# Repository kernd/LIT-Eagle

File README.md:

Eagle-Libraries
===============

holds all eagle files - projects and libraries

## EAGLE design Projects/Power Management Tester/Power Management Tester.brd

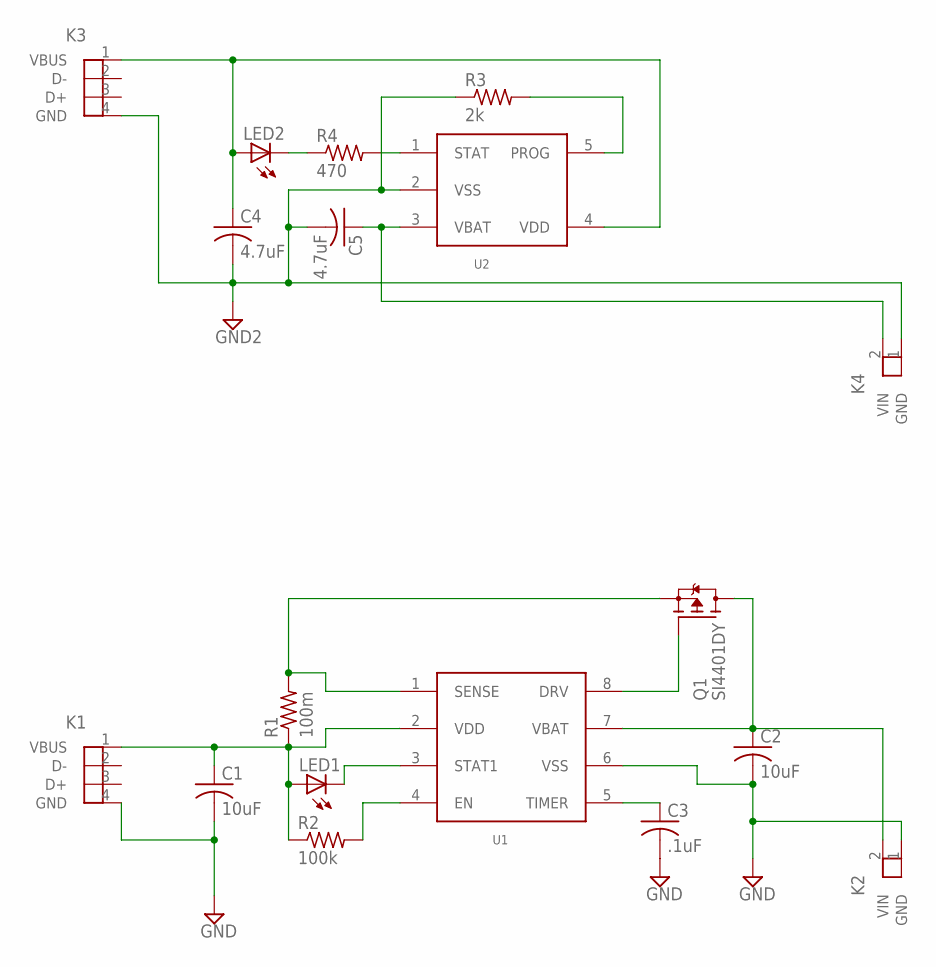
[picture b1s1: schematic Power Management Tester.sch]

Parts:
C1, C2: 10uF; 0805
C3: .1uF; 0603
C4, C5: 4.7uF; 0805
K1, K3: USBCONN; USB_RECEPT(CNC)
K2, K4: PWRCONN; 2CONN
LED1, LED2: LED0805; 0805
Q1: SI4401DY; 8-SOIC
R1: 100m; 0805
R2: 100k; 0603
R3: 2k; 0603
R4: 470; 0603
U1: MCP73843; 8-MSOP
U2: MCP73831; SOT-23

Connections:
5V_1: C1.A (1), K1.1 (VBUS), LED1.A (POS), R1.A (1), R2.1, U1.2 (VDD)
5V_2: C4.A (1), K3.1 (VBUS), LED2.A (POS), U2.4 (VDD)
D: C2.A (1), K2.2 (VIN), Q1.5 (D), Q1.6 (D), Q1.7 (D), Q1.8 (D), U1.7 (VBAT)
GND1: C1.A1 (2), C2.A1 (2), C3.2, K1.4 (GND), K2.1 (GND), U1.6 (VSS)
GND2: C4.A1 (2), C5.A1 (2), K3.4 (GND), K4.1 (GND), R3.1, U2.2 (VSS)
unnamed: C3.1, U1.5 (TIMER)
unnamed: LED2.A1 (NEG), R4.1
unnamed: R4.2, U2.1 (STAT)
unnamed: Q1.1 (S), Q1.2 (S), Q1.3 (S), R1.A1 (2), U1.1 (SENSE)
unnamed: LED1.A1 (NEG), U1.3 (STAT1)
unnamed: R2.2, U1.4 (EN)
unnamed: C5.A (1), K4.2 (VIN), U2.3 (VBAT)
unnamed: Q1.4 (G), U1.8 (DRV)
unnamed: R3.2, U2.5 (PROG)

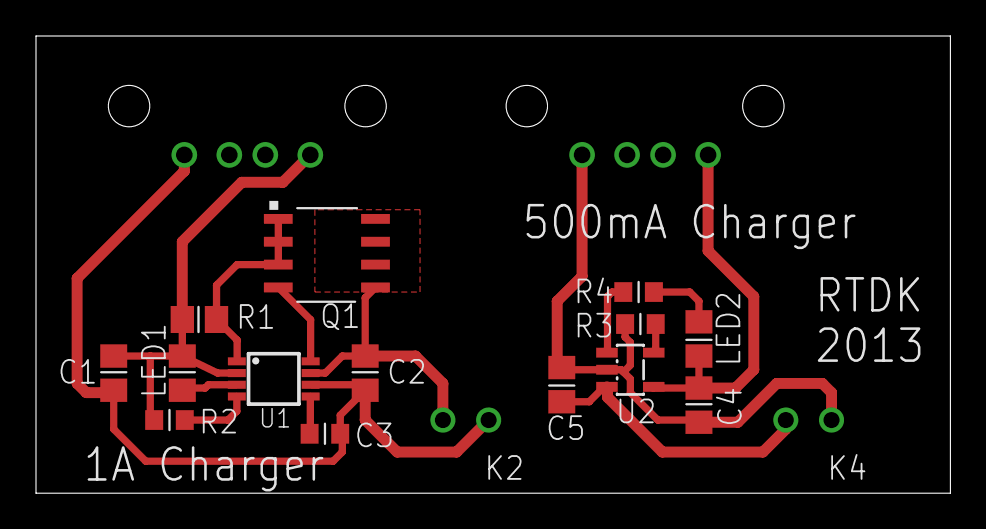
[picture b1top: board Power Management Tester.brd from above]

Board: 2 copper layers, 50.8 x 25.4 mm, 18 parts (0 on the bottom side), 14 nets.

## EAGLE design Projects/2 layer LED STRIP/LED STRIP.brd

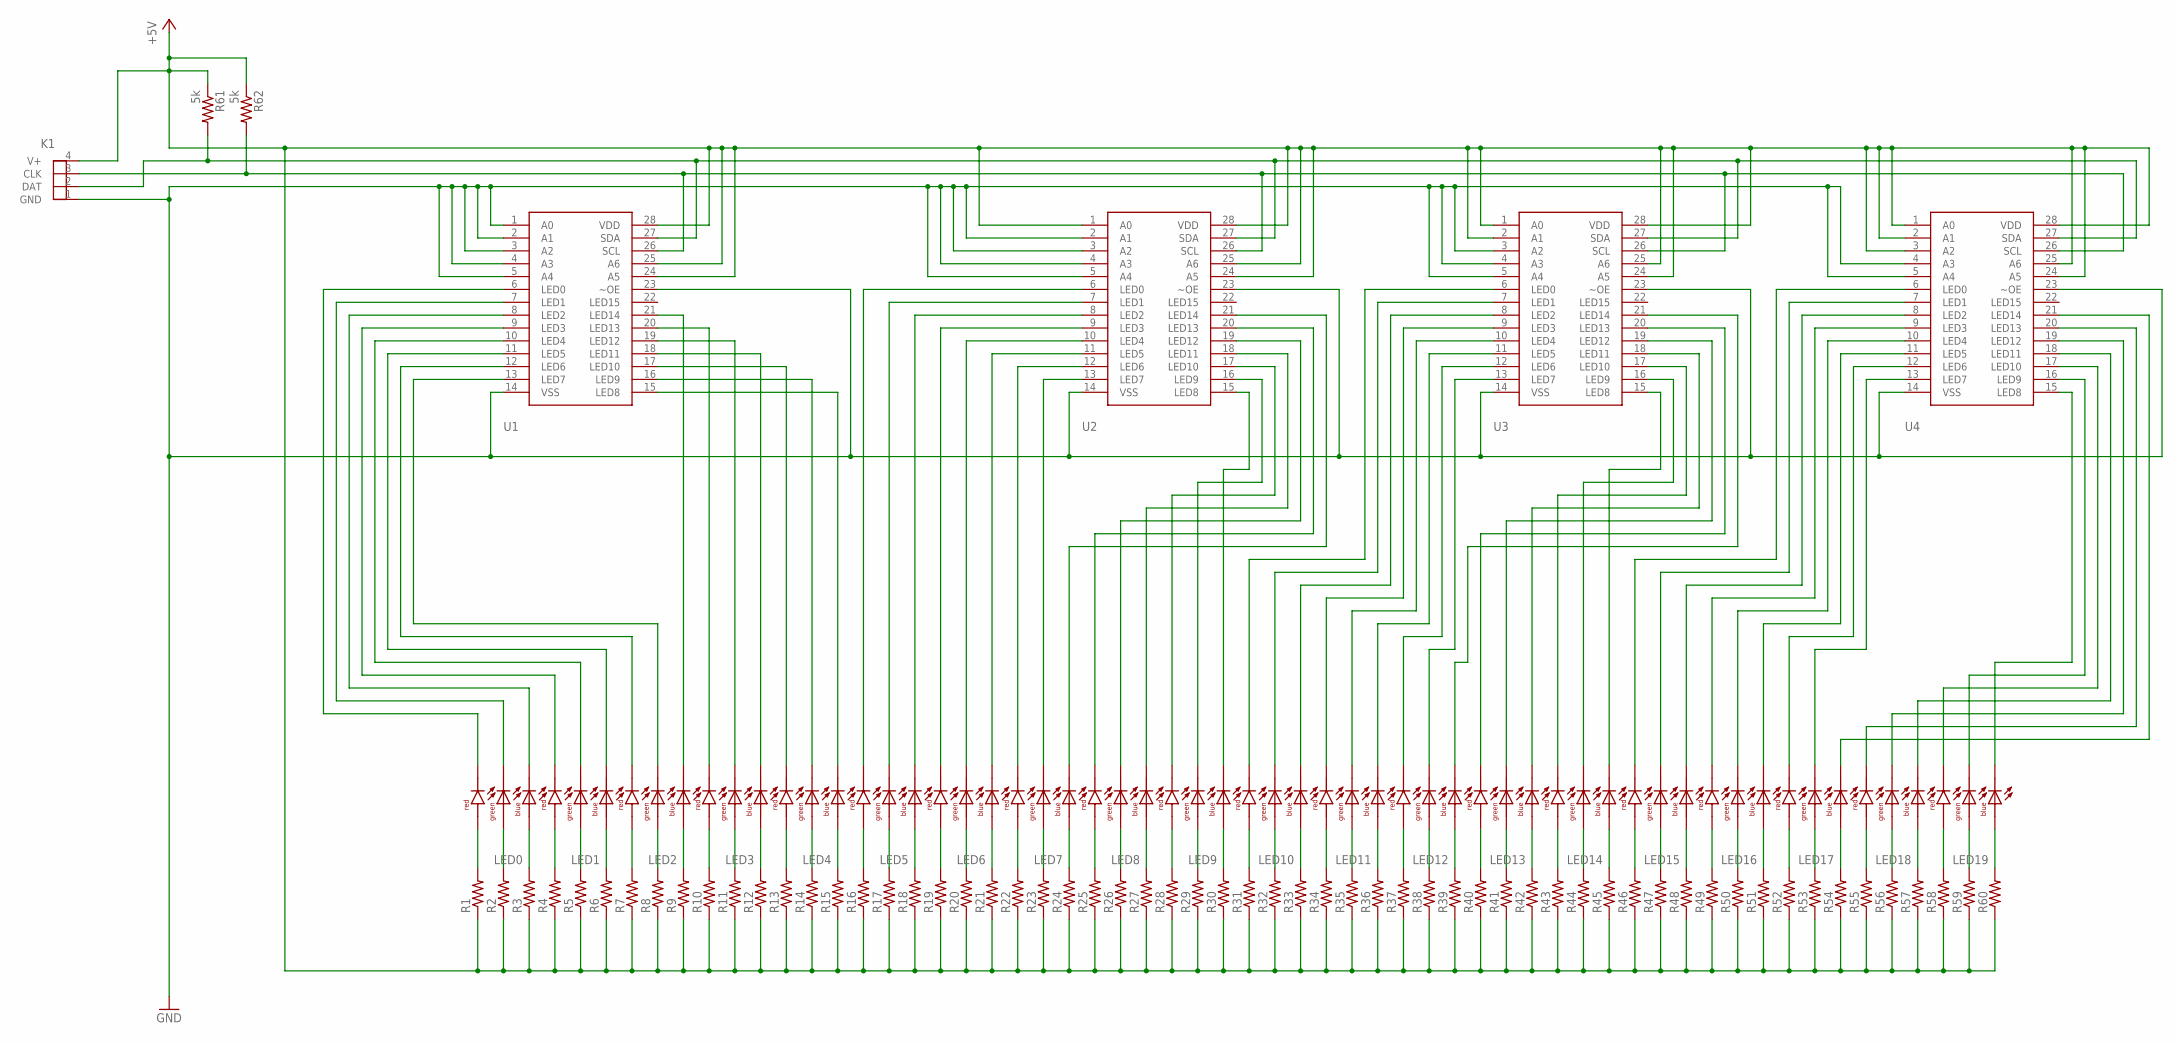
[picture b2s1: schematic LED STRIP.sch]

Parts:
K1: LEDCONN; 4CONN
LED0, LED1, LED2, LED3, LED4, LED5, LED6, LED7, LED8, LED9, LED10, LED11, LED12, LED13, LED14, LED15, LED16, LED17, LED18, LED19: LED_RGB; 6-PLCC
R1, R2, R3, R4, R5, R6, R7, R8, R9, R10, R11, R12, R13, R14, R15, R16, R17, R18, R19, R20, R21, R22, R23, R24, R25, R26, R27, R28, R29, R30, R31, R32, R33, R34, R35, R36, R37, R38, R39, R40, R41, R42, R43, R44, R45, R46, R47, R48, R49, R50, R51, R52, R53, R54, R55, R56, R57, R58, R59, R60: R0402; 0402
R61, R62: 5k; 0402
U1, U2, U3, U4: PCA9635; TSSOP28

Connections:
+5V: K1.4 (V+), R1.P$1 (1), R2.P$1 (1), R3.P$1 (1), R4.P$1 (1), R5.P$1 (1), R6.P$1 (1), R7.P$1 (1), R8.P$1 (1), R9.P$1 (1), R10.P$1 (1), R11.P$1 (1), R12.P$1 (1), R13.P$1 (1), R14.P$1 (1), R15.P$1 (1), R16.P$1 (1), R17.P$1 (1), R18.P$1 (1), R19.P$1 (1), R20.P$1 (1), R21.P$1 (1), R22.P$1 (1), R23.P$1 (1), R24.P$1 (1), R25.P$1 (1), R26.P$1 (1), R27.P$1 (1), R28.P$1 (1), R29.P$1 (1), R30.P$1 (1), R31.P$1 (1), R32.P$1 (1), R33.P$1 (1), R34.P$1 (1), R35.P$1 (1), R36.P$1 (1), R37.P$1 (1), R38.P$1 (1), R39.P$1 (1), R40.P$1 (1), R41.P$1 (1), R42.P$1 (1), R43.P$1 (1), R44.P$1 (1), R45.P$1 (1), R46.P$1 (1), R47.P$1 (1), R48.P$1 (1), R49.P$1 (1), R50.P$1 (1), R51.P$1 (1), R52.P$1 (1), R53.P$1 (1), R54.P$1 (1), R55.P$1 (1), R56.P$1 (1), R57.P$1 (1), R58.P$1 (1), R59.P$1 (1), R60.P$1 (1), R61.P$1 (1), R62.P$1 (1), U1.24 (A5), U1.25 (A6), U1.28 (VDD), U2.1 (A0), U2.24 (A5), U2.25 (A6), U2.28 (VDD), U3.1 (A0), U3.2 (A1), U3.24 (A5), U3.25 (A6), U3.28 (VDD), U4.1 (A0), U4.2 (A1), U4.3 (A2), U4.24 (A5), U4.25 (A6), U4.28 (VDD)
BLUE0: LED0.BLUE_LOW, U1.8 (LED2)
BLUE1: LED1.BLUE_LOW, U1.11 (LED5)
BLUE2: LED2.BLUE_LOW, U1.21 (LED14)
BLUE3: LED3.BLUE_LOW, U1.18 (LED11)
BLUE4: LED4.BLUE_LOW, U1.15 (LED8)
BLUE5: LED5.BLUE_LOW, U2.8 (LED2)
BLUE6: LED6.BLUE_LOW, U2.11 (LED5)
BLUE7: LED7.BLUE_LOW, U2.21 (LED14)
BLUE8: LED8.BLUE_LOW, U2.18 (LED11)
BLUE9: LED9.BLUE_LOW, U2.15 (LED8)
BLUE10: LED10.BLUE_LOW, U3.8 (LED2)
BLUE11: LED11.BLUE_LOW, U3.11 (LED5)
BLUE12: LED12.BLUE_LOW, U3.21 (LED14)
BLUE13: LED13.BLUE_LOW, U3.18 (LED11)
BLUE14: LED14.BLUE_LOW, U3.15 (LED8)
BLUE15: LED15.BLUE_LOW, U4.8 (LED2)
BLUE16: LED16.BLUE_LOW, U4.11 (LED5)
BLUE17: LED17.BLUE_LOW, U4.21 (LED14)
BLUE18: LED18.BLUE_LOW, U4.18 (LED11)
BLUE19: LED19.BLUE_LOW, U4.15 (LED8)
GND: K1.1 (GND), U1.1 (A0), U1.2 (A1), U1.3 (A2), U1.4 (A3), U1.5 (A4), U1.14 (VSS), U1.23 (~OE), U2.2 (A1), U2.3 (A2), U2.4 (A3), U2.5 (A4), U2.14 (VSS), U2.23 (~OE), U3.3 (A2), U3.4 (A3), U3.5 (A4), U3.14 (VSS), U3.23 (~OE), U4.4 (A3), U4.5 (A4), U4.14 (VSS), U4.23 (~OE)
GREEN0: LED0.GREEN_LOW, U1.7 (LED1)
GREEN1: LED1.GREEN_LOW, U1.10 (LED4)
GREEN2: LED2.GREEN_LOW, U1.13 (LED7)
GREEN3: LED3.GREEN_LOW, U1.19 (LED12)
GREEN4: LED4.GREEN_LOW, U1.16 (LED9)
GREEN5: LED5.GREEN_LOW, U2.7 (LED1)
GREEN6: LED6.GREEN_LOW, U2.10 (LED4)
GREEN7: LED7.GREEN_LOW, U2.13 (LED7)
GREEN8: LED8.GREEN_LOW, U2.19 (LED12)
GREEN9: LED9.GREEN_LOW, U2.16 (LED9)
GREEN10: LED10.GREEN_LOW, U3.7 (LED1)
GREEN11: LED11.GREEN_LOW, U3.10 (LED4)
GREEN12: LED12.GREEN_LOW, U3.13 (LED7)
GREEN13: LED13.GREEN_LOW, U3.19 (LED12)
GREEN14: LED14.GREEN_LOW, U3.16 (LED9)
GREEN15: LED15.GREEN_LOW, U4.7 (LED1)
GREEN16: LED16.GREEN_LOW, U4.10 (LED4)
GREEN17: LED17.GREEN_LOW, U4.13 (LED7)
GREEN18: LED18.GREEN_LOW, U4.19 (LED12)
GREEN19: LED19.GREEN_LOW, U4.16 (LED9)
unnamed: LED15.BLUE_HIGH, R48.P$2 (2)
unnamed: LED0.GREEN_HIGH, R2.P$2 (2)
unnamed: LED15.RED_HIGH, R46.P$2 (2)
unnamed: LED14.BLUE_HIGH, R45.P$2 (2)
unnamed: LED1.GREEN_HIGH, R5.P$2 (2)
unnamed: LED14.RED_HIGH, R43.P$2 (2)
unnamed: LED13.BLUE_HIGH, R42.P$2 (2)
unnamed: LED2.GREEN_HIGH, R8.P$2 (2)
unnamed: LED13.RED_HIGH, R40.P$2 (2)
unnamed: LED12.BLUE_HIGH, R39.P$2 (2)
unnamed: LED3.GREEN_HIGH, R11.P$2 (2)
unnamed: LED10.RED_HIGH, R31.P$2 (2)
unnamed: LED9.BLUE_HIGH, R30.P$2 (2)
unnamed: LED4.GREEN_HIGH, R14.P$2 (2)
unnamed: LED9.RED_HIGH, R28.P$2 (2)
unnamed: LED8.BLUE_HIGH, R27.P$2 (2)
unnamed: LED5.GREEN_HIGH, R17.P$2 (2)
unnamed: LED7.BLUE_HIGH, R24.P$2 (2)
unnamed: LED8.RED_HIGH, R25.P$2 (2)
unnamed: LED6.GREEN_HIGH, R20.P$2 (2)
unnamed: LED7.RED_HIGH, R22.P$2 (2)
unnamed: LED6.BLUE_HIGH, R21.P$2 (2)
unnamed: LED7.GREEN_HIGH, R23.P$2 (2)
unnamed: LED6.RED_HIGH, R19.P$2 (2)
unnamed: LED5.RED_HIGH, R16.P$2 (2)
unnamed: LED8.GREEN_HIGH, R26.P$2 (2)
unnamed: LED4.BLUE_HIGH, R15.P$2 (2)
unnamed: LED4.RED_HIGH, R13.P$2 (2)
unnamed: LED9.GREEN_HIGH, R29.P$2 (2)
unnamed: LED3.BLUE_HIGH, R12.P$2 (2)
unnamed: LED3.RED_HIGH, R10.P$2 (2)
unnamed: LED10.GREEN_HIGH, R32.P$2 (2)
unnamed: LED2.BLUE_HIGH, R9.P$2 (2)
unnamed: LED1.BLUE_HIGH, R6.P$2 (2)
unnamed: LED11.GREEN_HIGH, R35.P$2 (2)
unnamed: LED1.RED_HIGH, R4.P$2 (2)
unnamed: LED0.BLUE_HIGH, R3.P$2 (2)
unnamed: LED12.GREEN_HIGH, R38.P$2 (2)
unnamed: LED0.RED_HIGH, R1.P$2 (2)
unnamed: LED2.RED_HIGH, R7.P$2 (2)
unnamed: LED13.GREEN_HIGH, R41.P$2 (2)
unnamed: LED5.BLUE_HIGH, R18.P$2 (2)
unnamed: LED10.BLUE_HIGH, R33.P$2 (2)
unnamed: LED14.GREEN_HIGH, R44.P$2 (2)
unnamed: LED11.RED_HIGH, R34.P$2 (2)
unnamed: LED11.BLUE_HIGH, R36.P$2 (2)
unnamed: LED15.GREEN_HIGH, R47.P$2 (2)
unnamed: LED12.RED_HIGH, R37.P$2 (2)
unnamed: LED19.BLUE_HIGH, R60.P$2 (2)
unnamed: LED19.GREEN_HIGH, R59.P$2 (2)
unnamed: LED19.RED_HIGH, R58.P$2 (2)
unnamed: LED18.BLUE_HIGH, R57.P$2 (2)
unnamed: LED18.GREEN_HIGH, R56.P$2 (2)
unnamed: LED18.RED_HIGH, R55.P$2 (2)
unnamed: LED17.BLUE_HIGH, R54.P$2 (2)
unnamed: LED17.GREEN_HIGH, R53.P$2 (2)
unnamed: LED17.RED_HIGH, R52.P$2 (2)
unnamed: LED16.BLUE_HIGH, R51.P$2 (2)
unnamed: LED16.GREEN_HIGH, R50.P$2 (2)
unnamed: LED16.RED_HIGH, R49.P$2 (2)
RED0: LED0.RED_LOW, U1.6 (LED0)
RED1: LED1.RED_LOW, U1.9 (LED3)
RED2: LED2.RED_LOW, U1.12 (LED6)
RED3: LED3.RED_LOW, U1.20 (LED13)
RED4: LED4.RED_LOW, U1.17 (LED10)
RED5: LED5.RED_LOW, U2.6 (LED0)
RED6: LED6.RED_LOW, U2.9 (LED3)
RED7: LED7.RED_LOW, U2.12 (LED6)
RED8: LED8.RED_LOW, U2.20 (LED13)
RED9: LED9.RED_LOW, U2.17 (LED10)
RED10: LED10.RED_LOW, U3.6 (LED0)
RED11: LED11.RED_LOW, U3.9 (LED3)
RED12: LED12.RED_LOW, U3.12 (LED6)
RED13: LED13.RED_LOW, U3.20 (LED13)
RED14: LED14.RED_LOW, U3.17 (LED10)
RED15: LED15.RED_LOW, U4.6 (LED0)
RED16: LED16.RED_LOW, U4.9 (LED3)
RED17: LED17.RED_LOW, U4.12 (LED6)
RED18: LED18.RED_LOW, U4.20 (LED13)
RED19: LED19.RED_LOW, U4.17 (LED10)
SCL: K1.3 (CLK), R62.P$2 (2), U1.26 (SCL), U2.26 (SCL), U3.26 (SCL), U4.26 (SCL)
SDA: K1.2 (DAT), R61.P$2 (2), U1.27 (SDA), U2.27 (SDA), U3.27 (SDA), U4.27 (SDA)

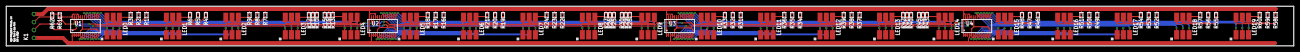
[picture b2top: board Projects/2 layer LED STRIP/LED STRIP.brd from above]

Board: 2 copper layers, 412.8 x 12.7 mm, 87 parts (0 on the bottom side), 124 nets.

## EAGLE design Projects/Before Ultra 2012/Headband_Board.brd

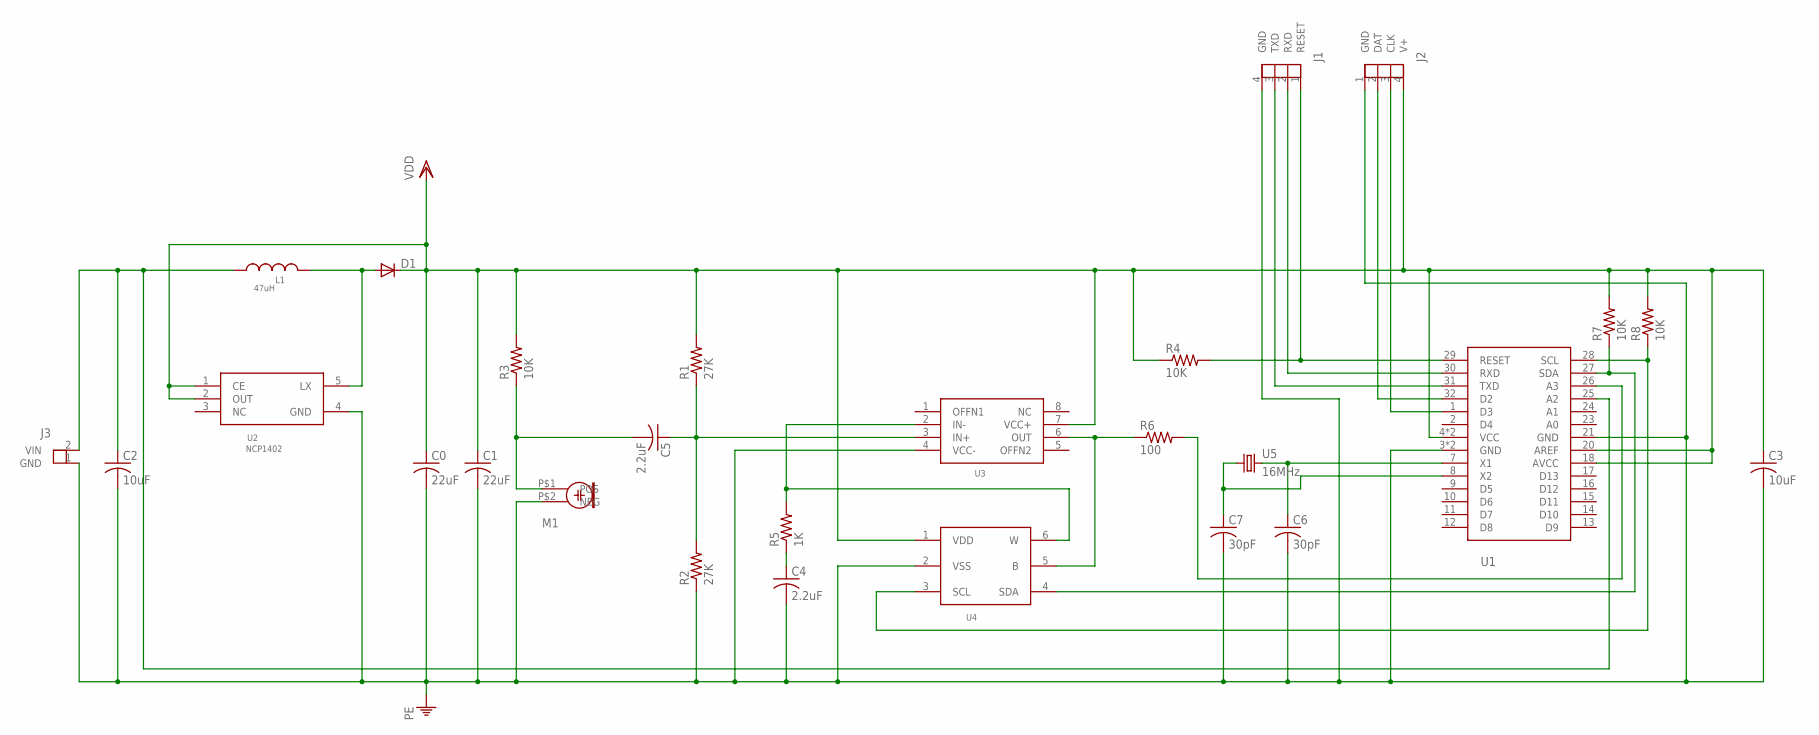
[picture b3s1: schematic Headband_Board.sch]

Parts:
C0, C1: 22uF; 0805
C2, C3: 10uF; 0805
C4, C5: 2.2uF; 0603
C6, C7: 30pF; 0603
D1: MBR0520LT; SOD-123
J1: PRGMCONN; 4CONN
J2: LEDCONN; 4CONN
J3: PWRCONN; 2CONN
L1: 47uH; INDUCPAC
M1: ELEC_MIC
R1, R2: 27K; 0603
R3, R4, R7, R8: 10K; 0603
R5: 1K; 0603
R6: 100; 0603
U1: ATMEGA328P; TQFP32-08
U2: NCP1402; TSOT-23-5
U3: TL071; 8-SOIC
U4: MCP4017; SOT-363
U5: 16MHz; HC49/US

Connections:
J1: J1.1 (RESET), R4.2, U1.29 (RESET)
unnamed: D1.A, L1.2, U2.5 (LX)
unnamed: C5.2, M1.P$1 (POS), R3.1
unnamed: R7.1, U1.27 (SDA), U4.4 (SDA)
unnamed: C5.1, R1.1, R2.2, U3.3 (IN+)
unnamed: R6.2, U1.26 (A3)
unnamed: C6.1, U1.7 (X1), U5.P$2 (2)
unnamed: C2.A (1), J3.2 (VIN), L1.3.7X1.2 (1), U1.25 (A2)
unnamed: J1.2 (RXD), U1.30 (RXD)
unnamed: C4.1, R5.1
unnamed: R5.2, U3.2 (IN-), U4.6 (W)
unnamed: J1.3 (TXD), U1.31 (TXD)
unnamed: R6.1, U3.6 (OUT), U4.5 (B)
unnamed: C7.1, U1.8 (X2), U5.P$1 (1)
unnamed: J2.2 (DAT), U1.32 (D2)
unnamed: J2.3 (CLK), U1.1 (D3)
unnamed: R8.1, U1.28 (SCL), U4.3 (SCL)
PE: C0.A1 (2), C1.A1 (2), C2.A1 (2), C3.A1 (2), C4.2, C6.2, C7.2, J1.4 (GND), J2.1 (GND), J3.1 (GND), M1.P$2 (NEG), R2.1, U1.3 (GND), U1.5 (GND), U1.21 (GND), U2.4 (GND), U3.4 (VCC-), U4.2 (VSS)
VDD: C0.A (1), C1.A (1), C3.A (1), D1.B, J2.4 (V+), R1.2, R3.2, R4.1, R7.2, R8.2, U1.4 (VCC), U1.6 (VCC), U1.18 (AVCC), U1.20 (AREF), U2.1 (CE), U2.2 (OUT), U3.7 (VCC+), U4.1 (VDD)

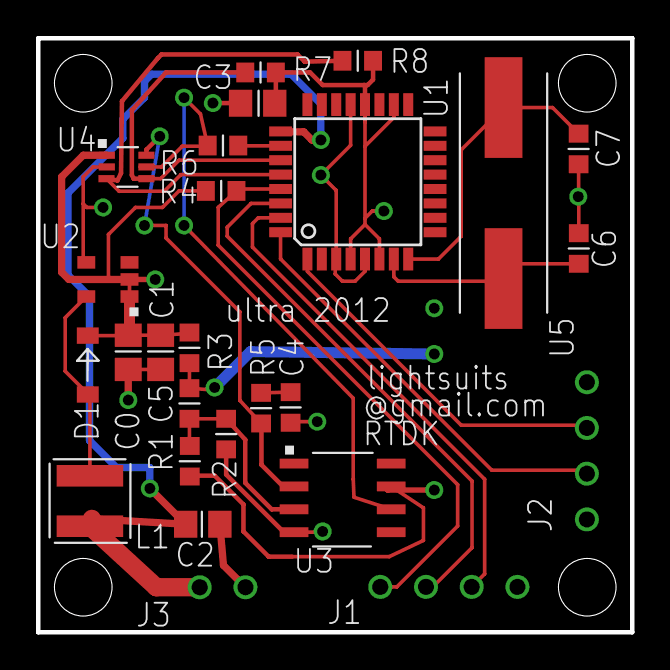
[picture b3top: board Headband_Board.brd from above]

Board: 2 copper layers, 33.0 x 33.0 mm, 27 parts (1 on the bottom side), 19 nets.

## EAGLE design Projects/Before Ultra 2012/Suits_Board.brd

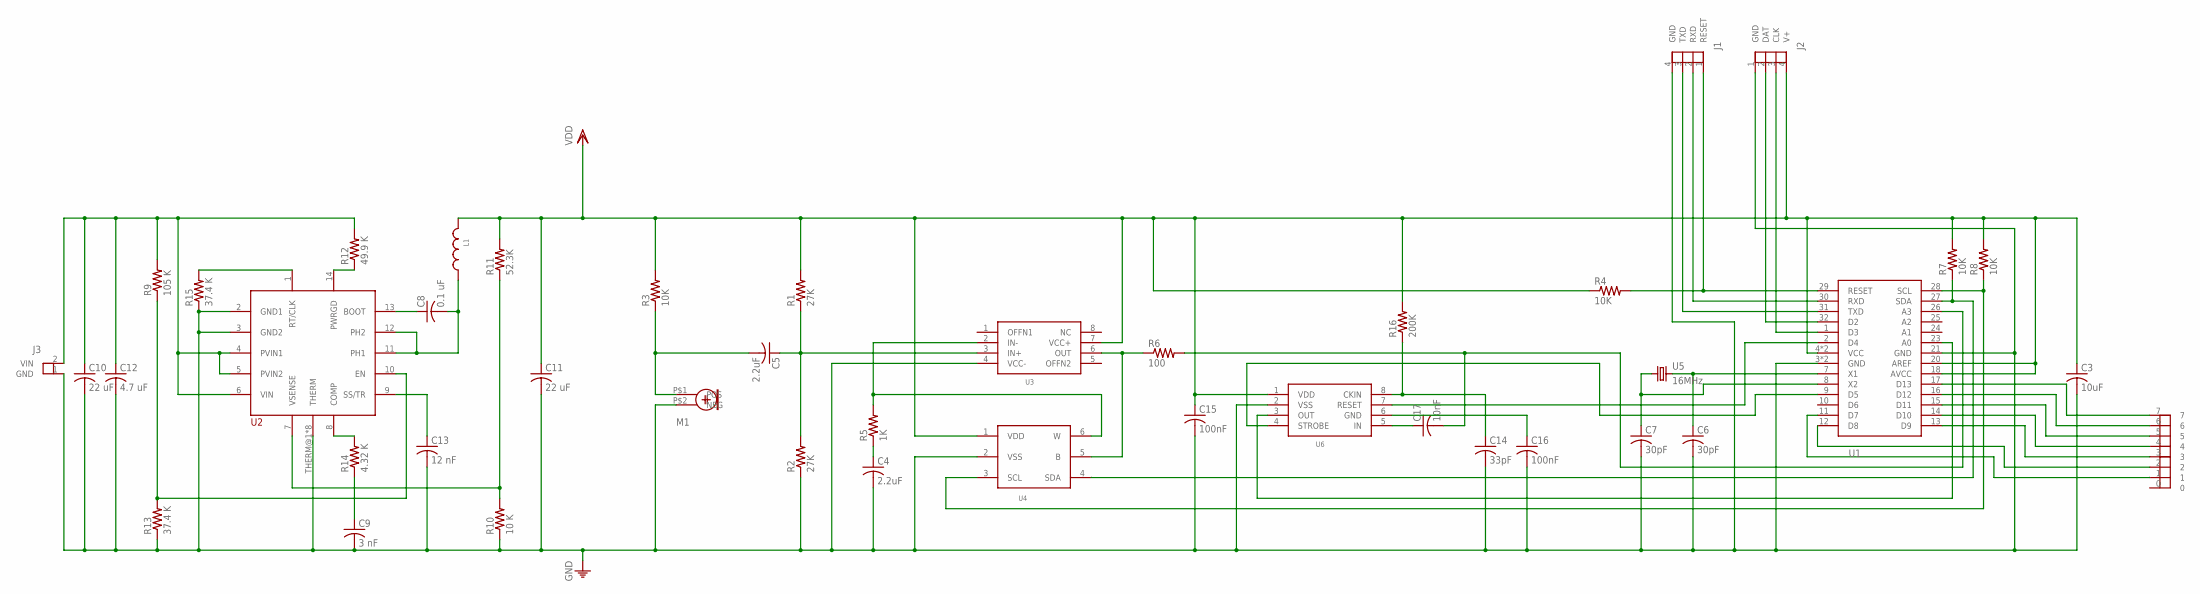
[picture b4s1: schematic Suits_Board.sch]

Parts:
C3: 10uF; 0805
C4, C5: 2.2uF; 0603
C6, C7: 30pF; 0603
C8: 0.1 uF; 0805
C9: 3 nF; 0805
C10, C11: 22 uF; 1210
C12: 4.7 uF; 0805
C13: 12 nF; 0402
C14: 33pF; 0402
C15, C16: 100nF; 0805
C17: 10nF; 0402
J1: PRGMCONN; 4CONN
J2: LEDCONN; 4CONN
J3: PWRCONN; 2CONN
L1: VLF10045T; VLF10045
M1: ELEC_MIC
R1, R2: 27K; 0603
R3, R4, R7, R8: 10K; 0603
R5: 1K; 0603
R6: 100; 0603
R9: 105 K; 0402
R10: 10 K; 0402
R11: 52.3K; 0402
R12: 49.9 K; 0402
R13, R15: 37.4 K; 0402
R14: 4.32 K; 0402
R16: 200K; 0603
U1: ATMEGA328P; TQFP32-08
U2: TPS54620; 14-VFQFN
U3: TL071; 8-SOIC
U4: MCP4017; SOT-363
U5: 16MHz; HC49/US
U6: FFT IC; DIP8
U$1: KEYPAD

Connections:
GND: C3.A1 (2), C4.2, C6.2, C7.2, C9.A1 (2), C10.P$2 (2), C11.P$2 (2), C12.A1 (2), C13.P$2 (2), C14.P$2 (2), C15.A1 (2), C16.A1 (2), J1.4 (GND), J2.1 (GND), J3.1 (GND), M1.P$2 (NEG), R2.1, R10.P$1 (1), R13.P$1 (1), R15.P$1 (1), U1.3 (GND), U1.5 (GND), U1.21 (GND), U2.2 (GND1), U2.3 (GND2), U2.THERM@1 (THERM), U2.THERM@2 (THERM), U2.THERM@3 (THERM), U2.THERM@4 (THERM), U2.THERM@5 (THERM), U2.THERM@6 (THERM), U2.THERM@7 (THERM), U2.THERM@8 (THERM), U3.4 (VCC-), U4.2 (VSS), U6.2 (VSS)
J1: J1.1 (RESET), R4.2, U1.29 (RESET)
unnamed: C14.P$1 (1), R16.1, U6.8 (CKIN)
unnamed: C16.A (1), U6.6 (GND)
unnamed: C5.2, M1.P$1 (POS), R3.1
unnamed: R7.1, U1.27 (SDA), U4.4 (SDA)
unnamed: C5.1, R1.1, R2.2, U3.3 (IN+)
unnamed: C17.P$2 (2), R6.2, U1.26 (A3)
unnamed: C6.1, U1.7 (X1), U5.P$2 (2)
unnamed: R14.P$2 (2), U2.8 (COMP)
unnamed: J1.2 (RXD), U1.30 (RXD)
unnamed: C4.1, R5.1
unnamed: R5.2, U3.2 (IN-), U4.6 (W)
unnamed: J1.3 (TXD), U1.31 (TXD)
unnamed: R6.1, U3.6 (OUT), U4.5 (B)
unnamed: U1.9 (D5), U6.4 (STROBE)
unnamed: J2.2 (DAT), U1.32 (D2)
unnamed: R9.P$1 (1), R13.P$2 (2), U2.10 (EN)
unnamed: J2.3 (CLK), U1.1 (D3)
unnamed: C9.A (1), R14.P$1 (1)
unnamed: R8.1, U1.28 (SCL), U4.3 (SCL)
unnamed: C13.P$1 (1), U2.9 (SS/TR)
unnamed: R15.P$2 (2), U2.1 (RT/CLK)
unnamed: R12.P$1 (1), U2.14 (PWRGD)
unnamed: C8.A1 (2), L1.P$1 (1), U2.11 (PH1), U2.12 (PH2)
unnamed: R10.P$2 (2), R11.P$1 (1), U2.7 (VSENSE)
unnamed: C8.A (1), U2.13 (BOOT)
unnamed: C17.P$1 (1), U6.5 (IN)
unnamed: U1.23 (A0), U6.3 (OUT)
unnamed: U1.17 (D13), U$1.7
unnamed: U1.15 (D11), U$1.5
unnamed: U1.16 (D12), U$1.6
unnamed: U1.14 (D10), U$1.4
unnamed: U1.13 (D9), U$1.3
unnamed: U1.12 (D8), U$1.2
unnamed: U1.11 (D7), U$1.1
unnamed: U1.2 (D4), U6.7 (RESET)
NAME\RIP: C7.1, U1.8 (X2), U5.P$1 (1)
VDD: C3.A (1), C11.P$1 (1), C15.A (1), J2.4 (V+), L1.P$2 (2), R1.2, R3.2, R4.1, R7.2, R8.2, R11.P$2 (2), R16.2, U1.4 (VCC), U1.6 (VCC), U1.18 (AVCC), U1.20 (AREF), U3.7 (VCC+), U4.1 (VDD), U6.1 (VDD)
VIN: C10.P$1 (1), C12.A (1), J3.2 (VIN), R9.P$2 (2), R12.P$2 (2), U2.4 (PVIN1), U2.5 (PVIN2), U2.6 (VIN)

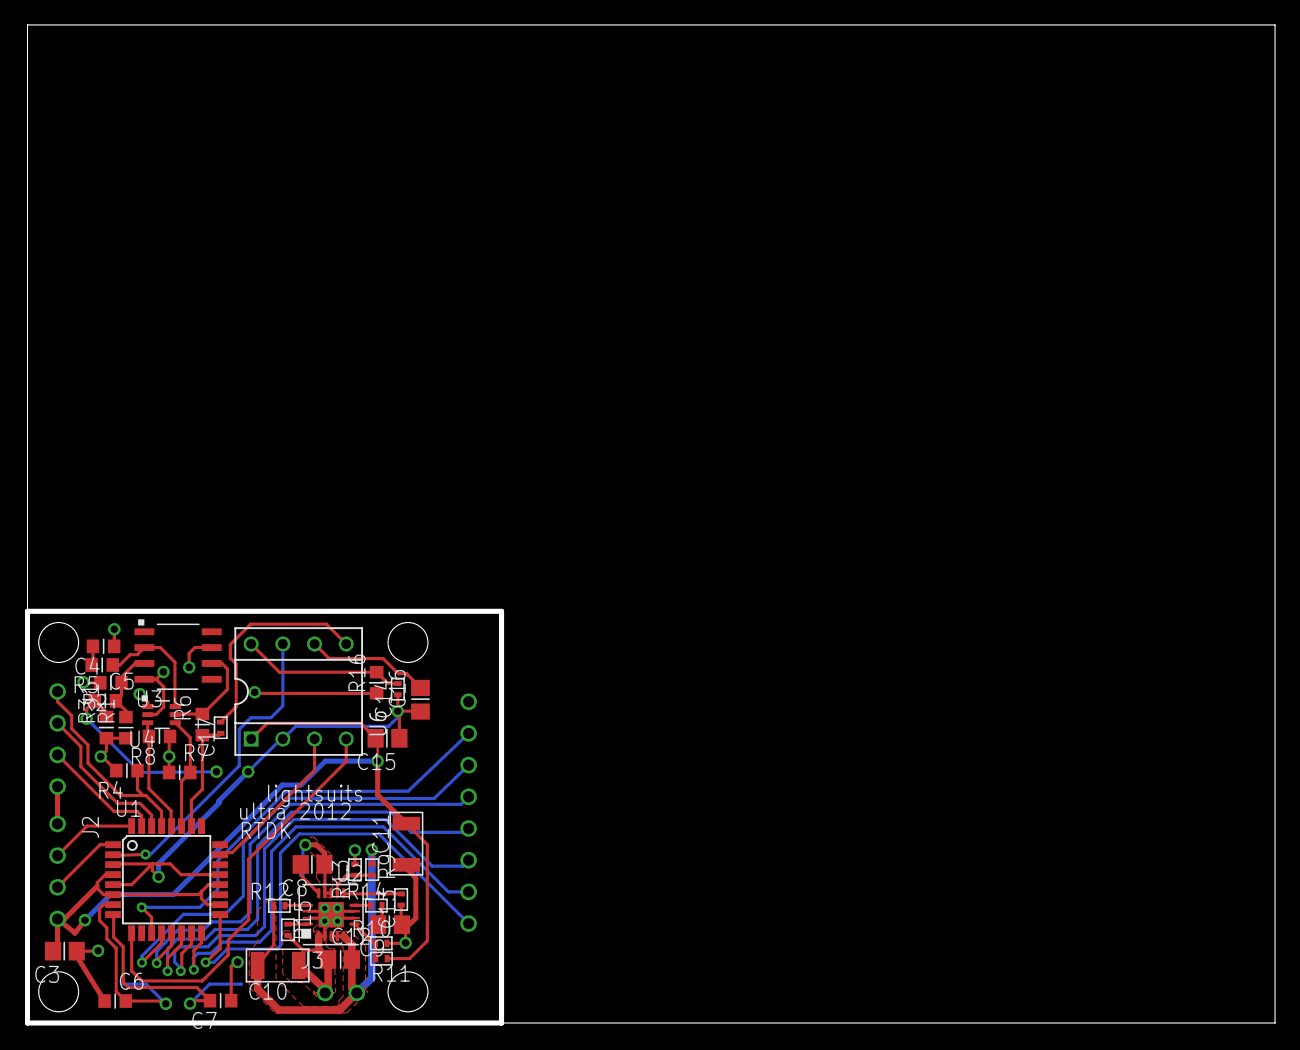
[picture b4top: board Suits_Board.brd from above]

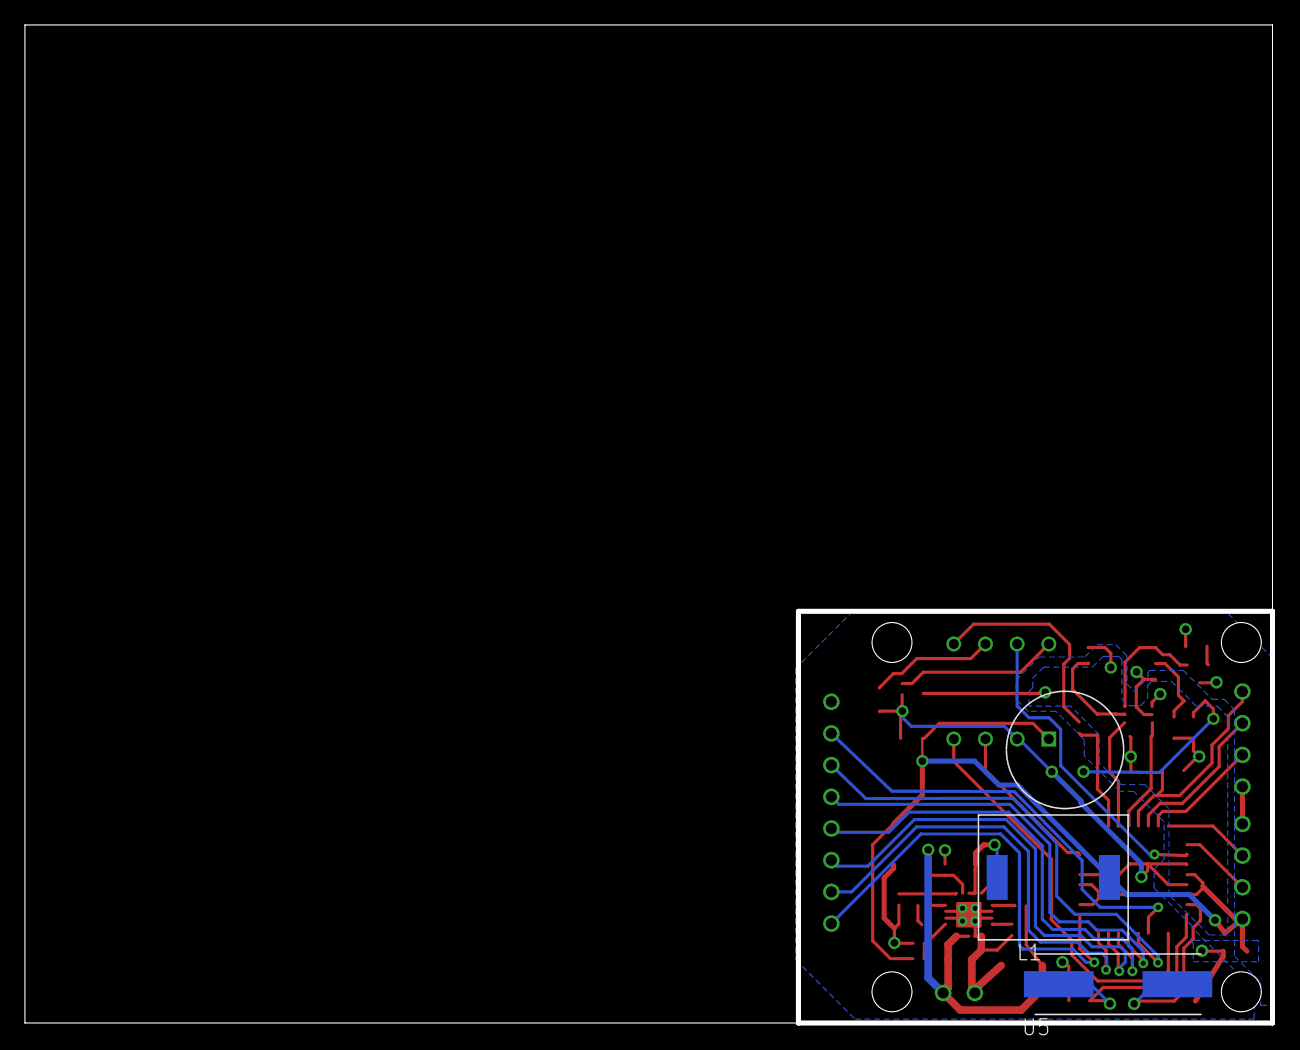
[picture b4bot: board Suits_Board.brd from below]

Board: 2 copper layers, 100.0 x 80.0 mm, 43 parts (3 on the bottom side), 40 nets.

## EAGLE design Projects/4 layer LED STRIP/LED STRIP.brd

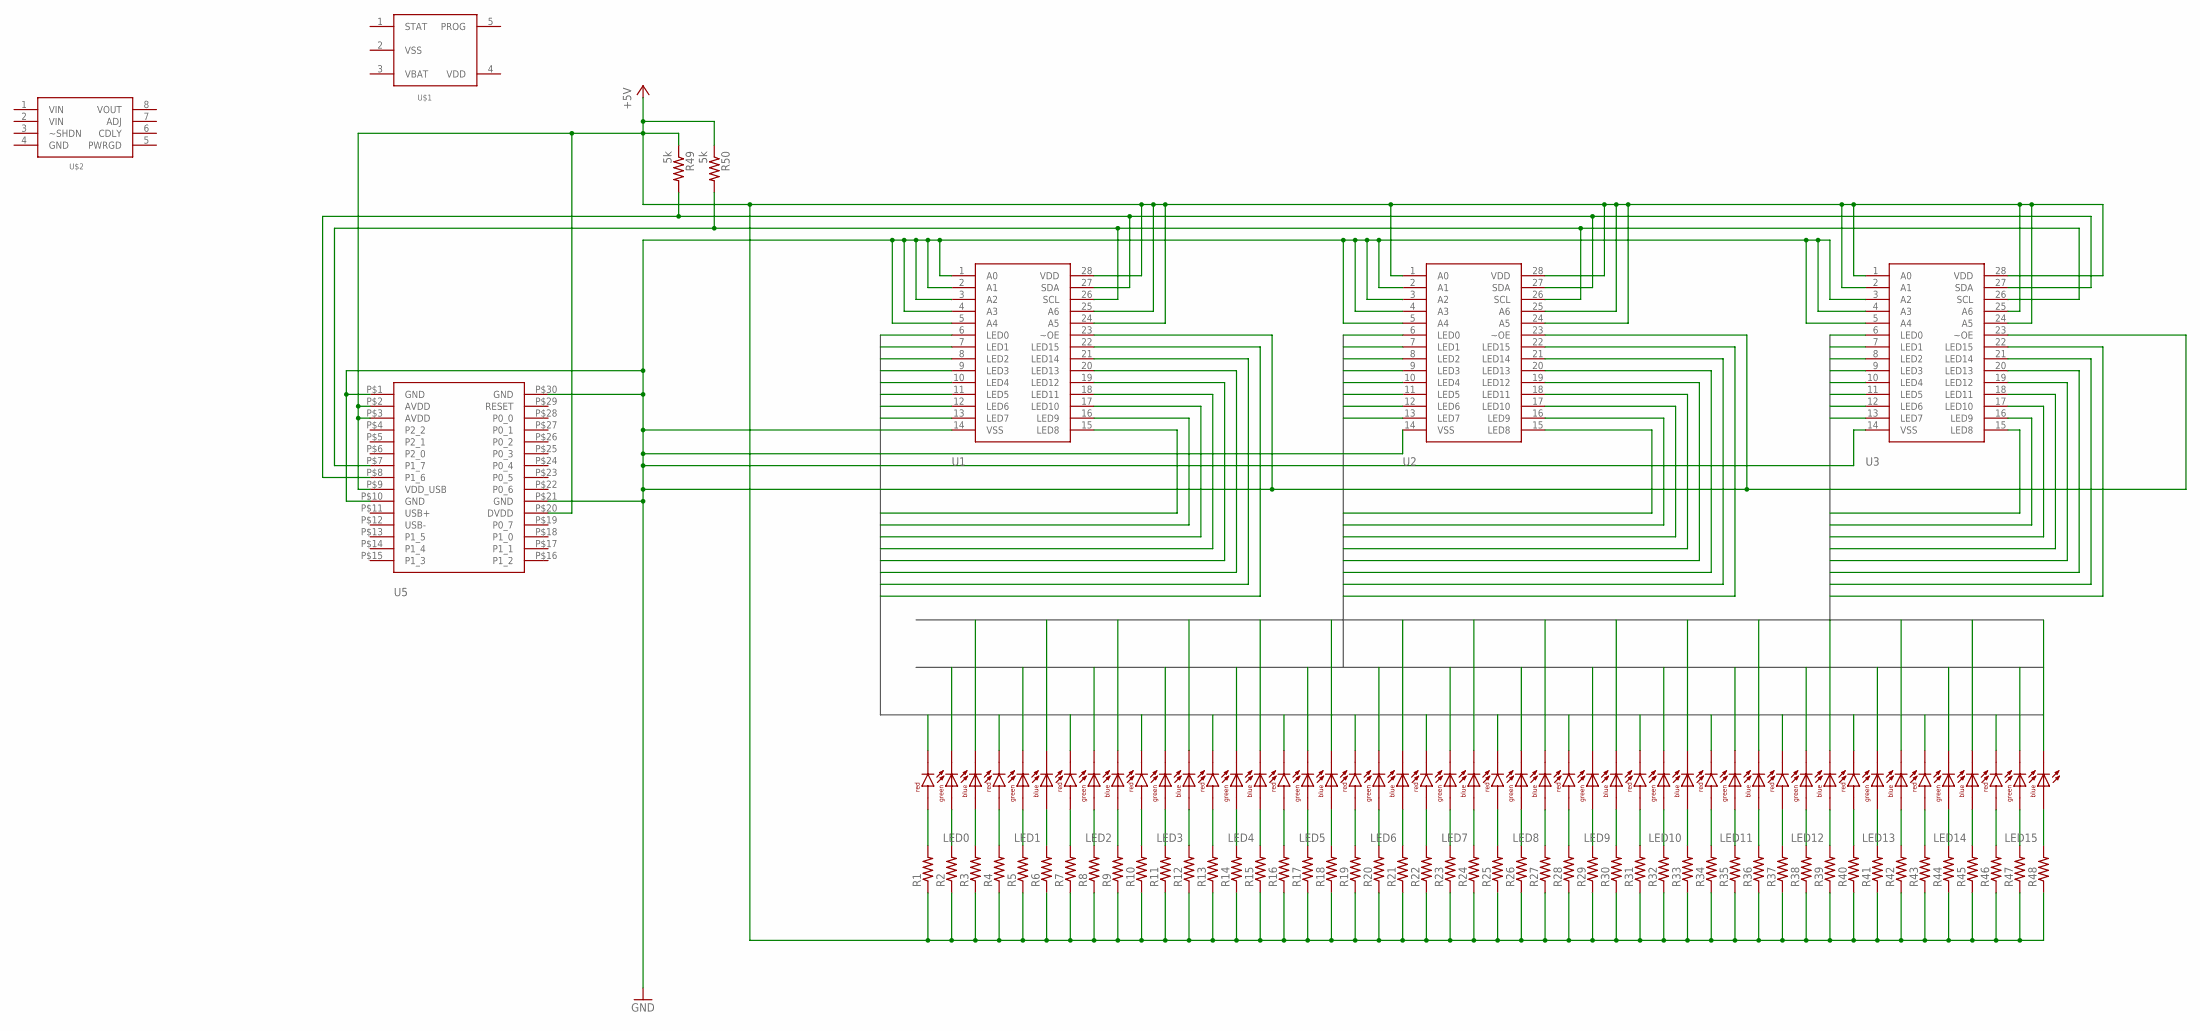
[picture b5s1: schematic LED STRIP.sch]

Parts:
LED0, LED1, LED2, LED3, LED4, LED5, LED6, LED7, LED8, LED9, LED10, LED11, LED12, LED13, LED14, LED15: LED_RGB; 6-PLCC
R1, R2, R3, R4, R5, R6, R7, R8, R9, R10, R11, R12, R13, R14, R15, R16, R17, R18, R19, R20, R21, R22, R23, R24, R25, R26, R27, R28, R29, R30, R31, R32, R33, R34, R35, R36, R37, R38, R39, R40, R41, R42, R43, R44, R45, R46, R47, R48: R0402; 0402
R49, R50: 5k; 0402
U1, U2, U3: PCA9635; TSSOP28
U5: BLE112
U$1: MCP73831; SOT-23
U$2: MCP1727; 8-SOIC

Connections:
+5V: R1.P$1 (1), R2.P$1 (1), R3.P$1 (1), R4.P$1 (1), R5.P$1 (1), R6.P$1 (1), R7.P$1 (1), R8.P$1 (1), R9.P$1 (1), R10.P$1 (1), R11.P$1 (1), R12.P$1 (1), R13.P$1 (1), R14.P$1 (1), R15.P$1 (1), R16.P$1 (1), R17.P$1 (1), R18.P$1 (1), R19.P$1 (1), R20.P$1 (1), R21.P$1 (1), R22.P$1 (1), R23.P$1 (1), R24.P$1 (1), R25.P$1 (1), R26.P$1 (1), R27.P$1 (1), R28.P$1 (1), R29.P$1 (1), R30.P$1 (1), R31.P$1 (1), R32.P$1 (1), R33.P$1 (1), R34.P$1 (1), R35.P$1 (1), R36.P$1 (1), R37.P$1 (1), R38.P$1 (1), R39.P$1 (1), R40.P$1 (1), R41.P$1 (1), R42.P$1 (1), R43.P$1 (1), R44.P$1 (1), R45.P$1 (1), R46.P$1 (1), R47.P$1 (1), R48.P$1 (1), R49.P$1 (1), R50.P$1 (1), U1.24 (A5), U1.25 (A6), U1.28 (VDD), U2.1 (A0), U2.24 (A5), U2.25 (A6), U2.28 (VDD), U3.1 (A0), U3.2 (A1), U3.24 (A5), U3.25 (A6), U3.28 (VDD), U5.P$2 (AVDD), U5.P$3 (AVDD), U5.P$9 (VDD_USB), U5.P$20 (DVDD)
BLUE0: LED0.1, U3.6 (LED0)
BLUE1: LED1.1, U3.7 (LED1)
BLUE2: LED2.1, U3.8 (LED2)
BLUE3: LED3.1, U3.9 (LED3)
BLUE4: LED4.1, U3.10 (LED4)
BLUE5: LED5.1, U3.11 (LED5)
BLUE6: LED6.1, U3.12 (LED6)
BLUE7: LED7.1, U3.13 (LED7)
BLUE8: LED8.1, U3.15 (LED8)
BLUE9: LED9.1, U3.16 (LED9)
BLUE10: LED10.1, U3.17 (LED10)
BLUE11: LED11.1, U3.18 (LED11)
BLUE12: LED12.1, U3.19 (LED12)
BLUE13: LED13.1, U3.20 (LED13)
BLUE14: LED14.1, U3.21 (LED14)
BLUE15: LED15.1, U3.22 (LED15)
GND: U1.1 (A0), U1.2 (A1), U1.3 (A2), U1.4 (A3), U1.5 (A4), U1.14 (VSS), U1.23 (~OE), U2.2 (A1), U2.3 (A2), U2.4 (A3), U2.5 (A4), U2.14 (VSS), U2.23 (~OE), U3.3 (A2), U3.4 (A3), U3.5 (A4), U3.14 (VSS), U3.23 (~OE), U5.P$1 (GND), U5.P$10 (GND), U5.P$21 (GND), U5.P$30 (GND)
GREEN0: LED0.2, U2.6 (LED0)
GREEN1: LED1.2, U2.7 (LED1)
GREEN2: LED2.2, U2.8 (LED2)
GREEN3: LED3.2, U2.9 (LED3)
GREEN4: LED4.2, U2.10 (LED4)
GREEN5: LED5.2, U2.11 (LED5)
GREEN6: LED6.2, U2.12 (LED6)
GREEN7: LED7.2, U2.13 (LED7)
GREEN8: LED8.2, U2.15 (LED8)
GREEN9: LED9.2, U2.16 (LED9)
GREEN10: LED10.2, U2.17 (LED10)
GREEN11: LED11.2, U2.18 (LED11)
GREEN12: LED12.2, U2.19 (LED12)
GREEN13: LED13.2, U2.20 (LED13)
GREEN14: LED14.2, U2.21 (LED14)
GREEN15: LED15.2, U2.22 (LED15)
unnamed: LED15.6, R48.P$2 (2)
unnamed: LED0.5, R2.P$2 (2)
unnamed: LED15.4, R46.P$2 (2)
unnamed: LED14.6, R45.P$2 (2)
unnamed: LED1.5, R5.P$2 (2)
unnamed: LED14.4, R43.P$2 (2)
unnamed: LED13.6, R42.P$2 (2)
unnamed: LED2.5, R8.P$2 (2)
unnamed: LED13.4, R40.P$2 (2)
unnamed: LED12.6, R39.P$2 (2)
unnamed: LED3.5, R11.P$2 (2)
unnamed: LED10.4, R31.P$2 (2)
unnamed: LED9.6, R30.P$2 (2)
unnamed: LED4.5, R14.P$2 (2)
unnamed: LED9.4, R28.P$2 (2)
unnamed: LED8.6, R27.P$2 (2)
unnamed: LED5.5, R17.P$2 (2)
unnamed: LED7.6, R24.P$2 (2)
unnamed: LED8.4, R25.P$2 (2)
unnamed: LED6.5, R20.P$2 (2)
unnamed: LED7.4, R22.P$2 (2)
unnamed: LED6.6, R21.P$2 (2)
unnamed: LED7.5, R23.P$2 (2)
unnamed: LED6.4, R19.P$2 (2)
unnamed: LED5.4, R16.P$2 (2)
unnamed: LED8.5, R26.P$2 (2)
unnamed: LED4.6, R15.P$2 (2)
unnamed: LED4.4, R13.P$2 (2)
unnamed: LED9.5, R29.P$2 (2)
unnamed: LED3.6, R12.P$2 (2)
unnamed: LED3.4, R10.P$2 (2)
unnamed: LED10.5, R32.P$2 (2)
unnamed: LED2.6, R9.P$2 (2)
unnamed: LED1.6, R6.P$2 (2)
unnamed: LED11.5, R35.P$2 (2)
unnamed: LED1.4, R4.P$2 (2)
unnamed: LED0.6, R3.P$2 (2)
unnamed: LED12.5, R38.P$2 (2)
unnamed: LED0.4, R1.P$2 (2)
unnamed: LED2.4, R7.P$2 (2)
unnamed: LED13.5, R41.P$2 (2)
unnamed: LED5.6, R18.P$2 (2)
unnamed: LED10.6, R33.P$2 (2)
unnamed: LED14.5, R44.P$2 (2)
unnamed: LED11.4, R34.P$2 (2)
unnamed: LED11.6, R36.P$2 (2)
unnamed: LED15.5, R47.P$2 (2)
unnamed: LED12.4, R37.P$2 (2)
RED0: LED0.3, U1.6 (LED0)
RED1: LED1.3, U1.7 (LED1)
RED2: LED2.3, U1.8 (LED2)
RED3: LED3.3, U1.9 (LED3)
RED4: LED4.3, U1.10 (LED4)
RED5: LED5.3, U1.11 (LED5)
RED6: LED6.3, U1.12 (LED6)
RED7: LED7.3, U1.13 (LED7)
RED8: LED8.3, U1.15 (LED8)
RED9: LED9.3, U1.16 (LED9)
RED10: LED10.3, U1.17 (LED10)
RED11: LED11.3, U1.18 (LED11)
RED12: LED12.3, U1.19 (LED12)
RED13: LED13.3, U1.20 (LED13)
RED14: LED14.3, U1.21 (LED14)
RED15: LED15.3, U1.22 (LED15)
SCL: R50.P$2 (2), U1.26 (SCL), U2.26 (SCL), U3.26 (SCL), U5.P$7 (P1_7)
SDA: R49.P$2 (2), U1.27 (SDA), U2.27 (SDA), U3.27 (SDA), U5.P$8 (P1_6)

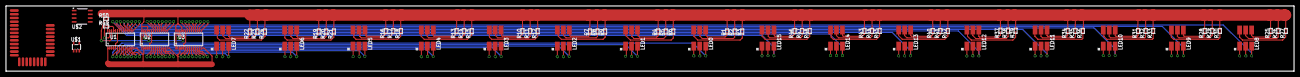
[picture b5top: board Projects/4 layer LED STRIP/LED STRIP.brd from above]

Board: 4 copper layers, 431.8 x 21.8 mm, 72 parts (0 on the bottom side), 100 nets.

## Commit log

2012-07-13 Update master
2012-07-13 initial commit - moved files from previous libraries and folder structure
    holds all libraries and previous project files for LIThreads
2012-07-13 rearranging folder structure
2012-07-13 deleteing unwanted files
2012-07-13 removing unwanted files
2012-07-13 adding projects from before ultra
2012-07-13 adding LED Strip Project
2012-07-13 moved SCL and SDA resistors to proper location
2012-08-11 updated board and schematic
    -changed PCA9635 library part. removed exposed pad and copied TSSOP28
    land pattern from another library
    -started routing some of the traces. decided on 4 layers
    -drill size of vias and trace width is not set in stone
2012-08-13 changed order of LEDs to make it more routable
2012-08-15 edited grid to imperial and corrected the nets of vias
2012-08-15 added LED8-LED15 traces from pads to local vias
2012-08-16 added traces that were accidentally deleted (from LED to via)
2012-08-16 added traces from ICs to bias
2012-08-17 lowered LED bias, changed order of LEDs to accommodate routing
2012-08-17 green and blue wired
2012-08-17 all traces for LED0-LED7 routed
2012-08-17 LED8-15 placed .9" spacing
2012-08-17 all LEDs wired to ICs
2012-08-17 relocated resistors
2012-08-17 resistors wired
2012-08-17 changed board size (shifted everything to the left)
2012-08-17 design is done. ERC, DRC, air wires all pass. next up: integrate bluetooth components
2013-01-09 adding power management files
2013-01-09 added back other projects (somehow were deleted on last commit)
2013-01-09 added battery management BOM
2013-01-16 added battery management parts
